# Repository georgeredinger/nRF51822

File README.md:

nRF51822
========

Diseño del Módulo nRF51822

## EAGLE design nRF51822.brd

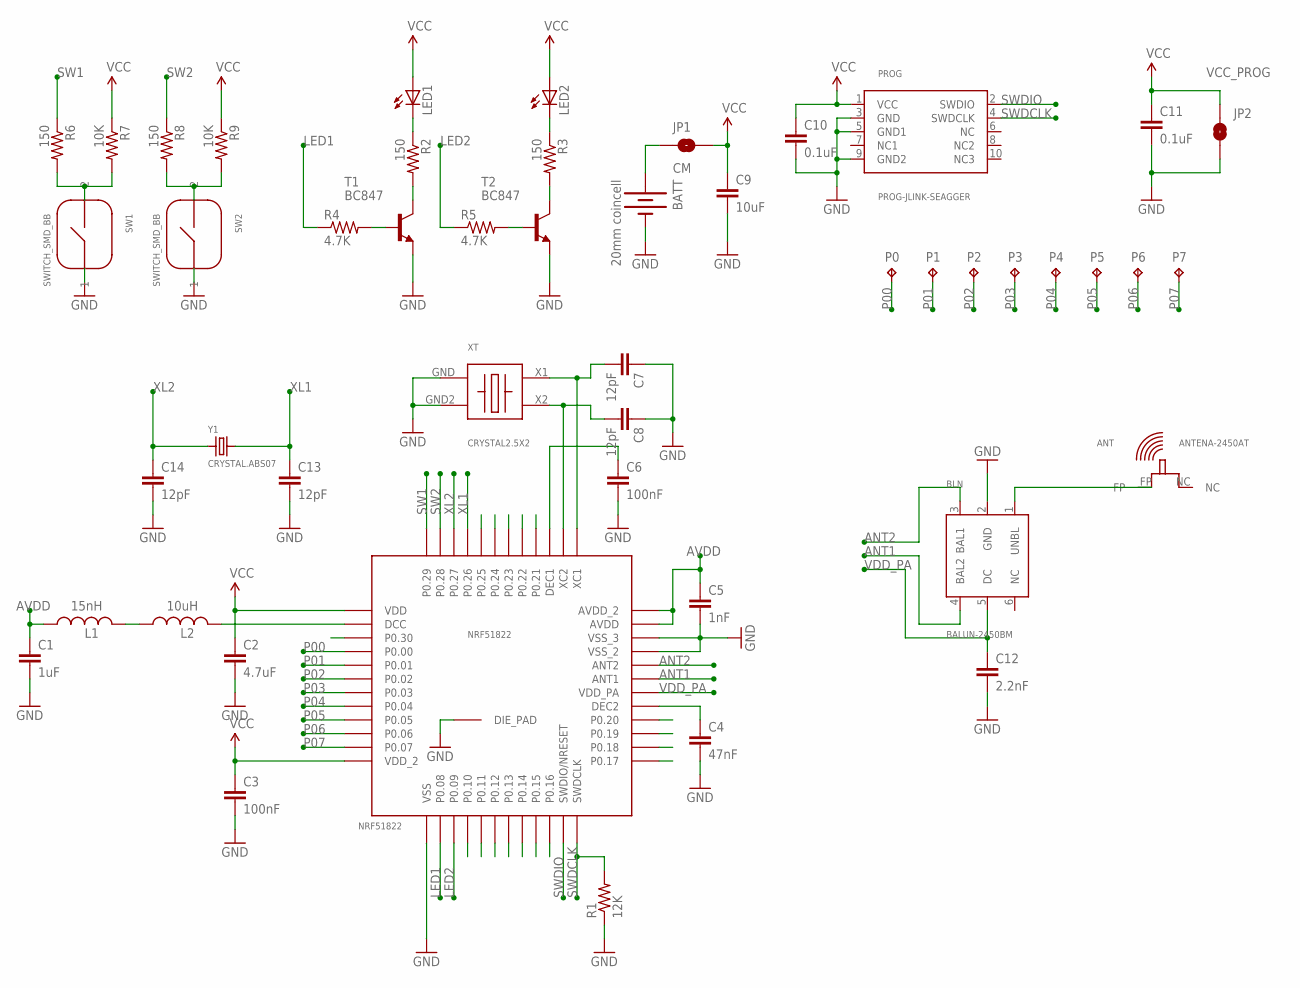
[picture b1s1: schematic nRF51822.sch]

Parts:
ANT: ANTENA-2450AT; 2450AT18B100
BATT: 20mm coincell; BATTCON_20MM_4LEGS_OVERPASTE
BLN: BALUN-2450BM; 2450BM14A0002
C1: 1uF; 0603-CAP
C2: 4.7uF; 0603-CAP
C3, C6: 100nF; 0603-CAP
C4: 47nF; 0603-CAP
C5: 1nF; 0603-CAP
C7, C8, C13, C14: 12pF; 0603-CAP
C9: 10uF; 0603-CAP
C10, C11: 0.1uF; 0603-CAP
C12: 2.2nF; 0603-CAP
JP1: CM; JUMP-0.05-SMD
JP2: VCC_PROG; JUMP-0.05-SMD
L1: 15nH; 0603
L2: 10uH; 0603
LED1, LED2: LED0603; LED-0603
NRF51822: NRF51822; QFN48
P0, P1, P2, P3, P4, P5, P6, P7: TPB1,27; B1,27
PROG: PROG-JLINK-SEAGGER; M50-3600742
R1: 12K; 0603-RES
R2, R3, R6, R8: 150; 0603-RES
R4, R5: 4.7K; 0603-RES
R7, R9: 10K; 0603-RES
SW1, SW2: SWITCH_SMD_BB; SWITCH3X2.5
T1, T2: BC847; SOT23
XT: CRYSTAL2.5X2; 2.5X2MM
Y1: CRYSTAL.ABS07; ABS07

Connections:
ANT1: BLN.4 (BAL2), NRF51822.31 (ANT1)
ANT2: BLN.3 (BAL1), NRF51822.32 (ANT2)
AVDD: C1.1, C5.1, L1.1, NRF51822.35 (AVDD), NRF51822.36 (AVDD_2)
GND: BATT.2 (-), BLN.2 (GND), C1.2, C2.2, C3.2, C4.2, C5.2, C6.2, C7.1, C8.1, C9.2, C10.2, C11.2, C12.2, C13.2, C14.2, JP2.P$2 (2), NRF51822.13 (VSS), NRF51822.33 (VSS_2), NRF51822.34 (VSS_3), NRF51822.GND (DIE_PAD), PROG.3 (GND), PROG.5 (GND1), PROG.9 (GND2), R1.1, SW1.1, SW2.1, T1.2 (E), T2.2 (E), XT.GND, XT.GND2
LED1: NRF51822.14 (P0.08), R4.1
LED2: NRF51822.15 (P0.09), R5.1
unnamed: C6.1, NRF51822.39 (DEC1)
unnamed: L1.2, L2.1
unnamed: L2.2, NRF51822.2 (DCC)
unnamed: C8.2, NRF51822.38 (XC2), XT.X2
unnamed: C7.2, NRF51822.37 (XC1), XT.X1
unnamed: C4.1, NRF51822.29 (DEC2)
unnamed: R5.2, T2.1 (B)
unnamed: BATT.1 (+), JP1.P$1 (1)
unnamed: R3.2, T2.3 (C)
unnamed: LED2.C, R3.1
unnamed: R8.2, R9.2, SW2.2
unnamed: R2.2, T1.3 (C)
unnamed: ANT.FP, BLN.1 (UNBL)
unnamed: LED1.C, R2.1
unnamed: R4.2, T1.1 (B)
unnamed: R6.2, R7.2, SW1.2
P00: NRF51822.4 (P0.00), P0.TP
P01: NRF51822.5 (P0.01), P1.TP
P02: NRF51822.6 (P0.02), P2.TP
P03: NRF51822.7 (P0.03), P3.TP
P04: NRF51822.8 (P0.04), P4.TP
P05: NRF51822.9 (P0.05), P5.TP
P06: NRF51822.10 (P0.06), P6.TP
P07: NRF51822.11 (P0.07), P7.TP
SW1: NRF51822.48 (P0.29), R6.1
SW2: NRF51822.47 (P0.28), R8.1
SWDCLK: NRF51822.24 (SWDCLK), PROG.4 (SWDCLK), R1.2
SWDIO: NRF51822.23 (SWDIO/NRESET), PROG.2 (SWDIO)
VCC: C2.1, C3.1, C9.1, C10.1, C11.1, JP1.P$2 (2), JP2.P$1 (1), LED1.A, LED2.A, NRF51822.1 (VDD), NRF51822.12 (VDD_2), PROG.1 (VCC), R7.1, R9.1
VDD_PA: BLN.5 (DC), C12.1, NRF51822.30 (VDD_PA)
XL1: C13.1, NRF51822.45 (P0.26), Y1.2
XL2: C14.1, NRF51822.46 (P0.27), Y1.1

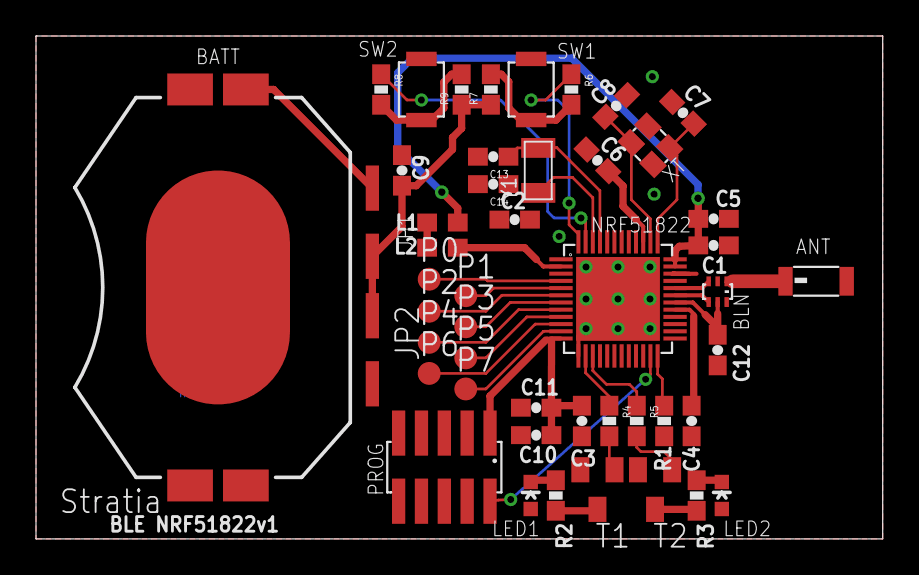
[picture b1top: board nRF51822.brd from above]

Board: 2 copper layers, 47.0 x 27.9 mm, 48 parts (0 on the bottom side), 38 nets.

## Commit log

2013-07-09 Diseno listo Esquematico
2013-07-09 anadi una tierra para test
2013-07-09 Test 2
2013-07-09 Nordic51822 Footprint
2013-07-09 BOM nRF51822
2013-07-09 Battery
2013-07-09 Update nRF51822 device
2013-07-09 CRYSTAL 16MHz Footprint
2013-07-09 Agregado de mas modulos
    Agregado Leds, Switchs y Alimentación
2013-07-10 Update Library
    Crystal, Conector de Programacion, Conector IO, Balun, Antena
2013-07-10 Update BOM
2013-07-10 Terminado el Esquemático
2013-07-10 Correccion Capacitores
    Correccion de los capacitores C1 y C2 del Crystal
2013-07-10 Tamaño de Letras
2013-07-11 Board 90%
2013-07-11 BOM 50%
2013-07-12 BLE NRF51822v1
    Board 100%, Lbr update Top places
2013-07-15 Gerber Files
2013-07-25 BOM Update
2013-07-25 Esquemático Rev 2
2013-08-01 Board V2 - 85%
2013-08-01 BOM Updated

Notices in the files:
parts and their libraries:
SparkFun-Capacitors: Licensing: CC v3.0 Share-Alike You are welcome to use this library for commercial purposes.
